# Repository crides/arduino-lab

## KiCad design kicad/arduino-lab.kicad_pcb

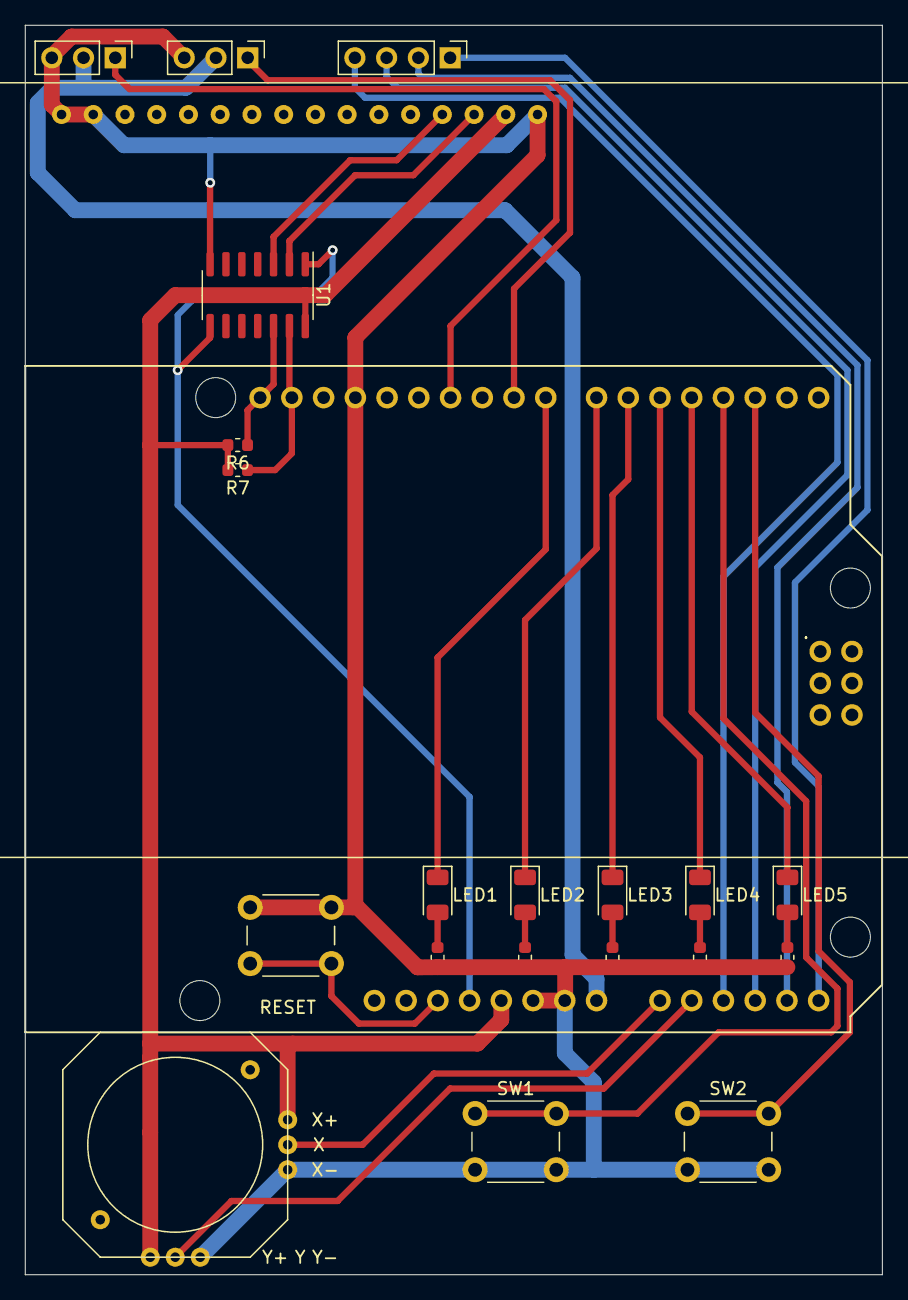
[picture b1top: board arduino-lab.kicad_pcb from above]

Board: 2 copper layers, 68.6 x 100.0 mm, 22 parts (0 on the bottom side), 29 nets.

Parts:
J1: joystick
J2, J3: Conn_01x03; PinHeader_1x03_P2.54mm_Vertical
J4: Conn_01x04; PinHeader_1x04_P2.54mm_Vertical
LCD1: LCD
LED1, LED2, LED3, LED4, LED5: LED; LED_1206_3216Metric
R1, R2, R3, R4, R5: 250; R_0603_1608Metric
R6, R7: 470; R_0603_1608Metric
SW1, SW2, SW3: SW_Push; SW_PUSH_6mm
U1: TXB0104D; SOIC-14_3.9x8.7mm_P1.27mm
XA1: Arduino_Uno_Shield

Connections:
3V3: U1.1, U1.8, XA1.3V3
5V: J1.1, J1.6, LCD1.15, R6.2, R7.2, U1.14, XA1.5V1
BTN1: SW1.1, XA1.D3
BTN2: SW2.1, XA1.D2
GND: J1.3, J1.4, J2.3, J3.3, LCD1.1, LCD1.2, LCD1.16, R1.2, R2.2, R3.2, R4.2, R5.2, SW1.2, SW2.2, SW3.2, U1.7, XA1.GND1, XA1.GND2, XA1.GND3
LED1: LED1.1, XA1.D8
LED2: LED2.1, XA1.D7
LED3: LED3.1, XA1.D6
LED4: LED4.1, XA1.D5
LED5: LED5.1, XA1.D4
unnamed: LED1.2, R1.1
unnamed: LED2.2, R2.1
unnamed: LED3.2, R3.1
unnamed: LED4.2, R4.1
unnamed: LED5.2, R5.1
RST: SW3.1, XA1.RST1
SCL3V3: LCD1.13, U1.3
SCL5: R6.1, U1.12, XA1.SCL
SDA3V3: LCD1.14, U1.2
SDA5: R7.1, U1.13, XA1.SDA
SERVO1: J3.1, XA1.D9
SERVO2: J2.1, XA1.D11
VIN: J2.2, J3.2, XA1.VIN
X: J1.2, XA1.A0
X+: J4.2, XA1.A4
X-: J4.4, XA1.A2
Y: J1.5, XA1.A1
Y+: J4.3, XA1.A3
Y-: J4.1, XA1.A5

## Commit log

2020-03-06 Rev1
2020-03-27 Working arduino sketch
2020-03-27 Added custom footprints
2020-03-27 Added arduino shields symbols and footprints
2020-03-27 Add gitignore
2020-03-27 Added kicad files
2020-03-27 Updated Gerbers
2020-03-27 Added board and schematics pdfs
2020-03-27 Added avr code
    finished with servo
2020-03-28 Added ADC and USART
2020-04-11 Added OLED code
    OLED is working, but could be optimized. It's not working when the lines
    waiting for BUSY is swapped in `i2c.c` in `i2c_send_buffer`. Reason is
    unknown for now.
2020-04-11 changed font size
2020-04-11 Fixed makefile
2020-04-11 Fix OLED
2020-04-11 Update PCB
2020-04-23 Add LED cycling
2020-04-23 Compacted layout of schematics
2020-04-23 Need to write to `PORT` before reading?
    reason unknown
